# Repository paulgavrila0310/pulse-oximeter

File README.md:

# pulse-oximeter

Device for measuring pulse and SpO2 levels

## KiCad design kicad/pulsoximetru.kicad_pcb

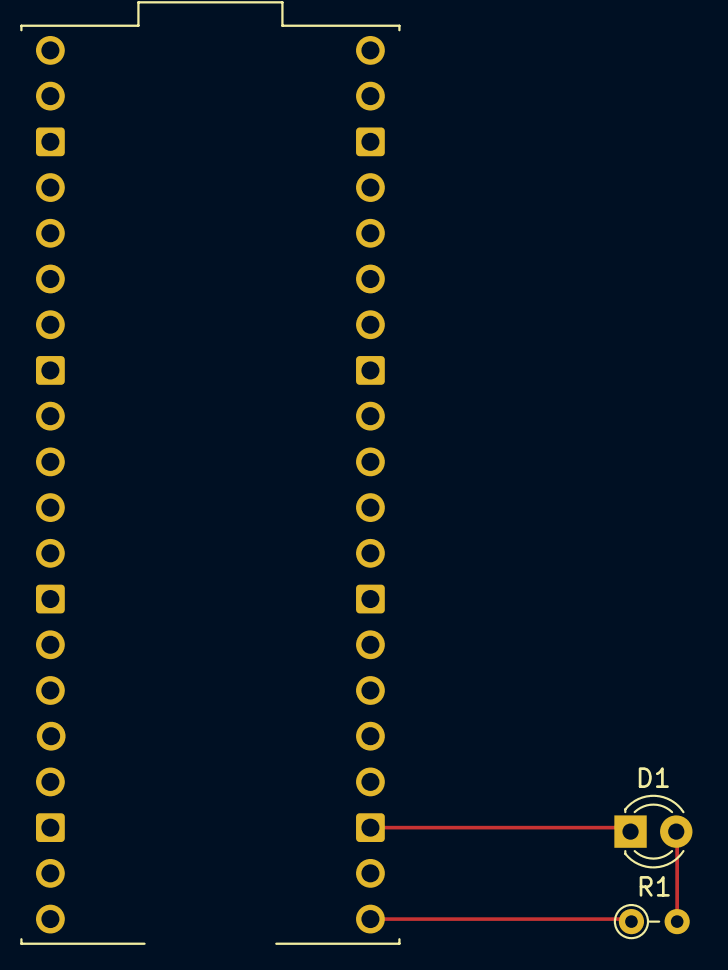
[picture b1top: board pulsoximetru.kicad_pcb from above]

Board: 2 copper layers, 3 parts (0 on the bottom side), 3 nets.

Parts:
A1: SC0918; MODULE_SC0918
D1: LED; LED_D3.0mm
R1: R; R_Axial_DIN0204_L3.6mm_D1.6mm_P2.54mm_Vertical

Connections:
GND: A1.3 (GND), A1.8 (GND), A1.13 (GND), A1.18 (GND), A1.23 (GND), A1.28 (GND), A1.33 (AGND), A1.38 (GND), D1.1 (K)
unnamed: A1.21 (GP16), R1.1
unnamed: D1.2 (A), R1.2

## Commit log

2025-03-06 Added the lab skel along with helpers
    This commit adds the lab skel containing a minimal embassy Pico 2W
    application and a utilities crate for wrapping embassy routines.
2025-03-07 added .vscode config files
2025-03-07 fixed wifi clock divider bug
2025-03-11 Updated main file
2025-03-15 Removed wifi module
2025-04-13 Add wifi utils
    Added functions and macro in the utils crate to help initialize the wifi
    chip driver and the network stack.
2025-05-20 kicad source files
2025-05-22 reading data from sensor
